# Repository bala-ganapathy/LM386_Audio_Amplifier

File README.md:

# LM386_Audio_Amplifier
It is a PCB design made by using KiCad software 
# LM386 Audio Amplifier

This repository contains the KiCad project files for a simple audio amplifier based on the LM386 IC. This amplifier is designed for low-power audio applications and is suitable for use with small speakers or headphones.

## Project Files

- **Schematic Diagram**: See `Project-LM386_Amp.kicad_sch`
- **PCB Layout**: See `Project-LM386_Amp.kicad_pcb`
- **Images**: See
  Schematic Diagram : 'Project-LM386_Amp-Schematic_Diag.png'
  PCB Diagram : 'Project-LM386_Amp_PCB-Diag.png'
  #d View : 'Project-LM386_Amp_3d-view.png'

## Design Overview

This audio amplifier uses the LM386 IC to amplify low audio signals. The PCB layout is optimized to reduce noise and improve signal integrity.

## Components

| Component | Value   | Purpose                       |
|-----------|---------|-------------------------------|
| LM386     | -       | Amplifier IC                  |
| C_in1     | 10 µF   | Input Coupling Capacitor      |
| C_out1    | 220 µF  | Output Coupling Capacitor     |
| C_power1  | 100 µF  | Power Supply Bypass Capacitor |
| J_audio1  | -       | Audio Input Connector         |
| J_power1  | -       | Power Connector               |
| J_speaker1| -       | Speaker Output Connector      |

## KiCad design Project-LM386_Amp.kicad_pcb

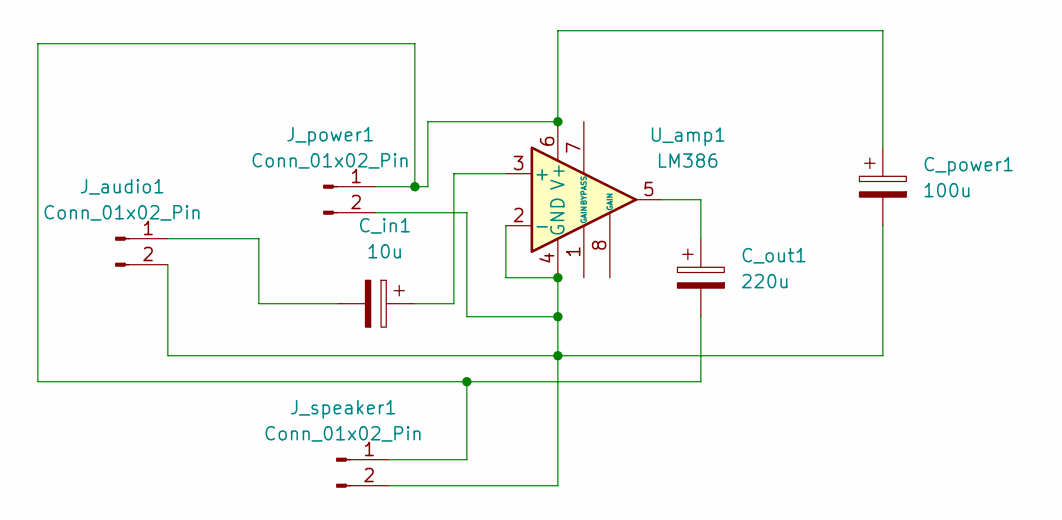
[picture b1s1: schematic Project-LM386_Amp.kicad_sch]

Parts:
C_in1: 10u; CP_Elec_6.3x5.3
C_out1: 220u; CP_Elec_6.3x5.3
C_power1: 100u; CP_Elec_6.3x5.3
J_audio1: Conn_01x02_Pin; PinHeader_1x02_P2.54mm_Vertical
J_power1: Conn_01x02_Pin; PinHeader_1x02_P2.54mm_Vertical
J_speaker1: Conn_01x02_Pin; PinHeader_1x02_P2.54mm_Vertical
U_amp1: LM386; HSOP-8-1EP_3.9x4.9mm_P1.27mm_EP2.3x2.3mm

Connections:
unnamed: C_out1.1, U_amp1.5
unnamed: C_in1.2, J_audio1.1
unnamed: C_power1.2, J_audio1.2, J_power1.2, J_speaker1.2, U_amp1.2 (-), U_amp1.4 (GND)
unnamed: C_out1.2, C_power1.1, J_power1.1, J_speaker1.1, U_amp1.6 (V+)
unnamed: C_in1.1, U_amp1.3 (+)

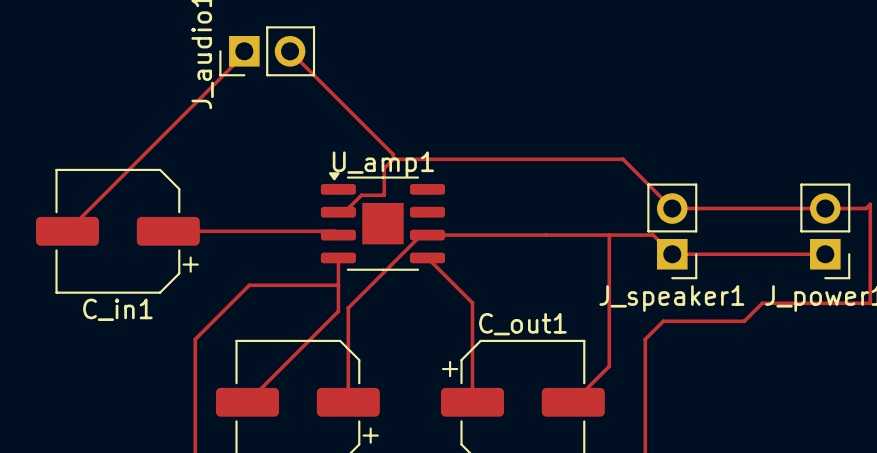
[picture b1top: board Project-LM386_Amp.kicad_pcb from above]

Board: 2 copper layers, 7 parts (0 on the bottom side), 5 nets.
